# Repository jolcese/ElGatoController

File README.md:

# EL Gato Controller

  ## Description
  This is a standalone controller for the ElGato Lights. It's based on an ESP-WROOM-32 module but any ESP32 (or even ESP8266) should work with minimal changes.

  <figure><figcaption>Controller with Display and 3D Printed Case</figcaption></figure>
  <br>
  <br>
  <figure><figcaption>Schematic for the module, USB-UART controller and buttons</figcaption></figure>
  <br>
  <figure><figcaption>Display has been added after designing the PCB so no header/connector</figcaption></figure>
  <br>

  ## Table of Contents
  * [ToDo](#todo)
  * [Installation](#installation)
  * [Usage](#usage)
  * [License](#license)
  * [Contributing](#contributing)
  * [Tests](#tests)
  * [Questions](#questions)

  ## ToDo
  
  - NTP
  - Dynamic lights config/ Web Server
  - Shortcut reboot
  - Brightness
  - Faster REST
  - FIx BAR size
  - ~Wifi Portal~
  - ~OLED Status~
  ## Installation
  Some of the tools used to build this project
  - [Plaftormio](https://platformio.org/)
  - [Kicad](https://www.kicad.org/)
  ## Usage
  Currently, the IPs for both lights are hardcoded. Until I made that discoverable thru Bonjour, numbers of lights and IPs will need to be manually mofified.
  
    main.cpp
    
    const String sLight1 = "192.168.30.137";
    const String sLight2 = "192.168.30.161";

  ## License
  This project is license under MIT

  ## Contributing
  Nothing

  ## Tests
  no tests

  ## Questions
  If you have any questions about this projects, please contact me directly at jolcese@gmail.com. You can view more of my projects at https://github.com/jolcese.

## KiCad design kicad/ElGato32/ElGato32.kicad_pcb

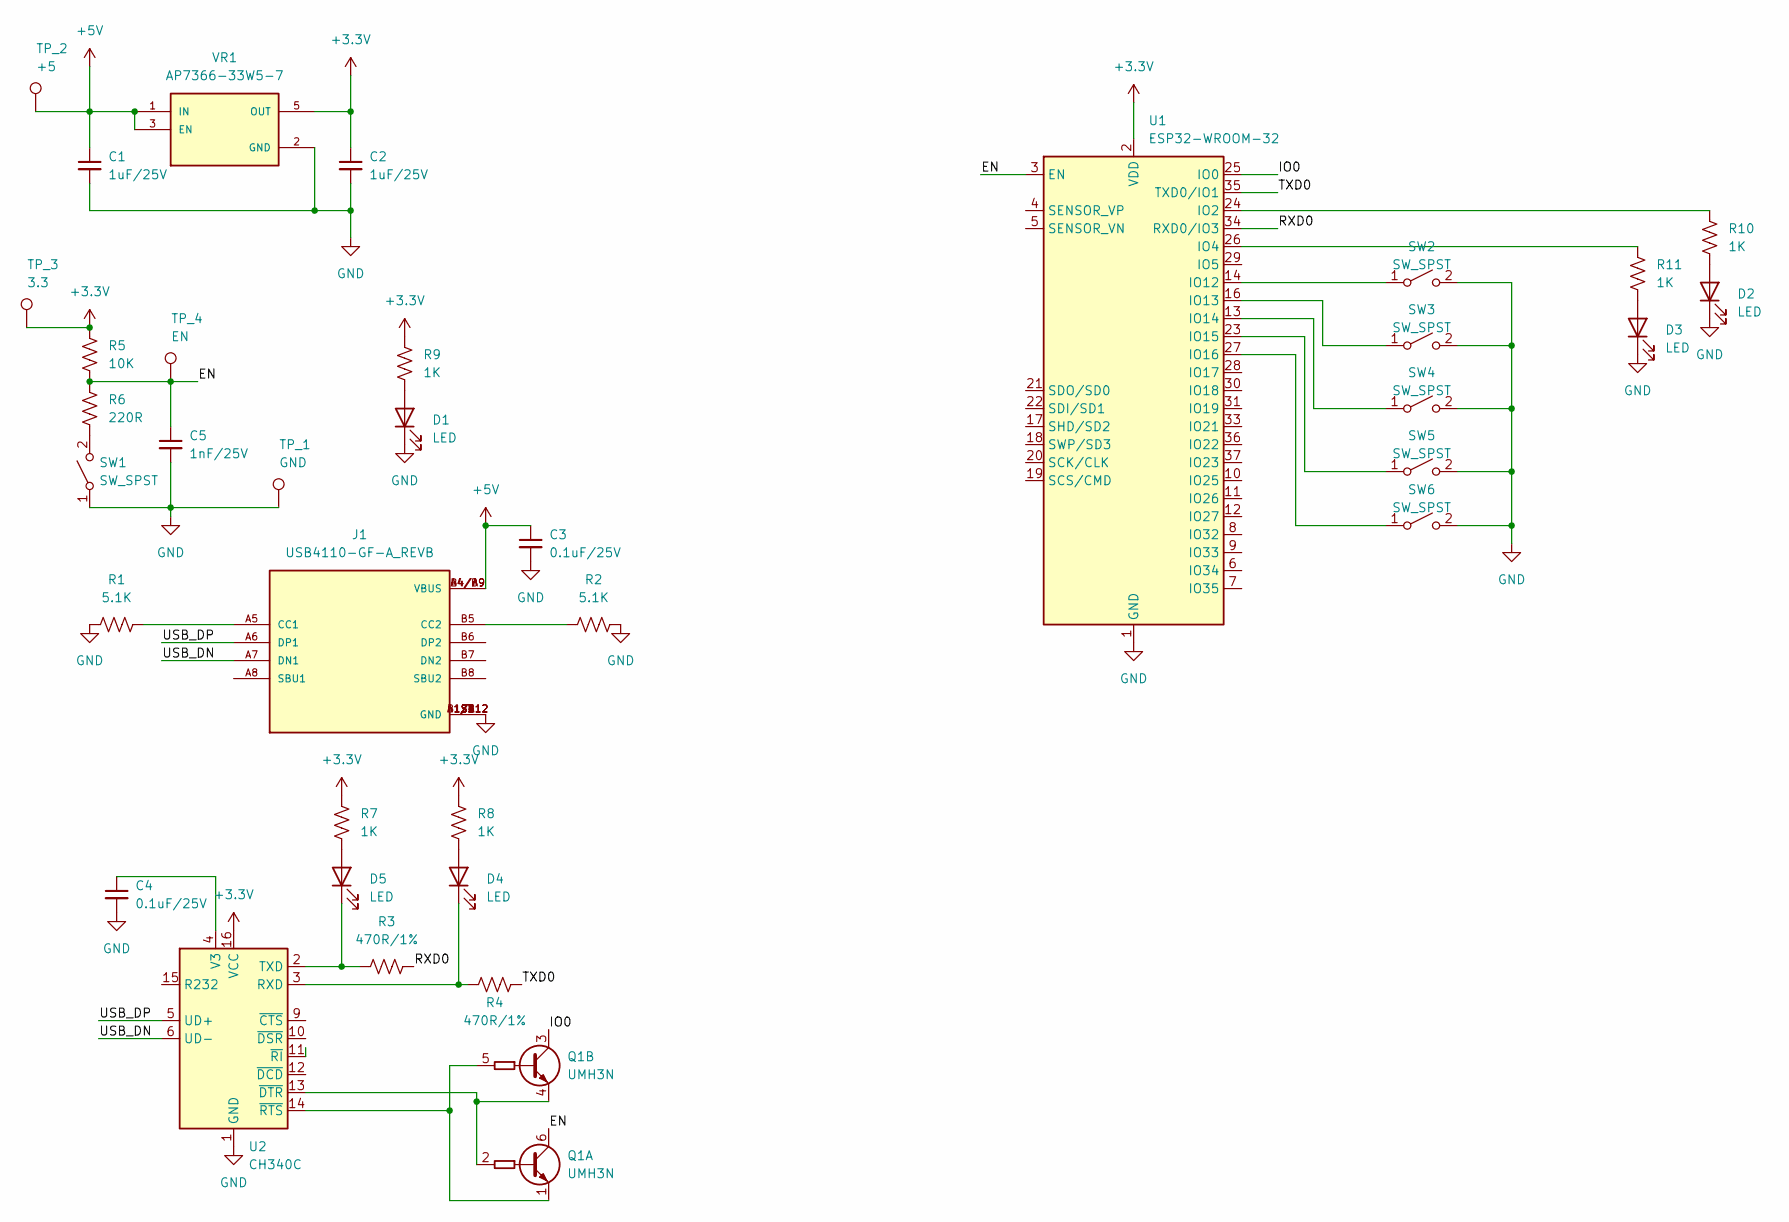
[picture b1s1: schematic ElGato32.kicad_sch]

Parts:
C1, C2: 1uF/25V; C_1206_3216Metric
C3, C4: 0.1uF/25V; C_1206_3216Metric
C5: 1nF/25V; C_1206_3216Metric
D1, D2, D3, D4, D5: LED; LED_1206_3216Metric_Pad1.42x1.75mm_HandSolder
J1: USB4110-GF-A_REVB; GCT_USB4110-GF-A_REVB; PARTREV B
Q1: UMH3N; SOT-363_SC-70-6
R1, R2: 5.1K; R_1206_3216Metric
R3, R4: 470R/1%; R_1206_3216Metric
R5: 10K; R_1206_3216Metric
R6: 220R; R_1206_3216Metric
R7, R8, R9, R10, R11: 1K; R_1206_3216Metric
SW1: SW_SPST; SW_B3U-3000P
SW2, SW3, SW4, SW5, SW6: SW_SPST; SW_PUSH-12mm
TP_1: GND; TestPoint_THTPad_1.5x1.5mm_Drill0.7mm
TP_2: +5; TestPoint_THTPad_1.5x1.5mm_Drill0.7mm
TP_3: 3.3; TestPoint_THTPad_1.5x1.5mm_Drill0.7mm
TP_4: EN; TestPoint_THTPad_1.5x1.5mm_Drill0.7mm
U1: ESP32-WROOM-32
U2: CH340C; SOIC-16_3.9x9.9mm_P1.27mm
VR1: AP7366-33W5-7; SOT95P285X140-5N; PARTREV 1-2

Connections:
+3.3V: C2.1, R5.2, R7.2, R8.2, R9.2, TP_3.1, U1.2 (VDD), U2.16 (VCC), VR1.5 (OUT)
+5V: C1.1, C3.1, J1.A4/B9 (VBUS), J1.B4/A9 (VBUS), TP_2.1, VR1.1 (IN), VR1.3 (EN)
/EN: C5.1, Q1.6 (C1), R5.1, R6.2, TP_4.1, U1.3 (EN)
/IO0: Q1.3 (C2), U1.25 (IO0)
/RXD0: R3.2, U1.34 (RXD0/IO3)
/TXD0: R4.2, U1.35 (TXD0/IO1)
/USB_DN: J1.A7 (DN1), U2.6 (UD-)
/USB_DP: J1.A6 (DP1), U2.5 (UD+)
GND: C1.2, C2.2, C3.2, C4.2, C5.2, D1.1 (K), D2.1 (K), D3.1 (K), J1.A1/B12 (GND), J1.B1/A12 (GND), J1.S1 (GND), J1.S2 (GND), J1.S3 (GND), J1.S4 (GND), R1.1, R2.2, SW1.1 (A), SW2.2 (B), SW3.2 (B), SW4.2 (B), SW5.2 (B), SW6.2 (B), TP_1.1, U1.1 (GND), U1.15 (GND), U1.38 (GND), U1.39 (GND), U2.1 (GND), VR1.2 (GND)
unnamed: D1.2 (A), R9.1
unnamed: D2.2 (A), R10.1
unnamed: D3.2 (A), R11.1
unnamed: D4.2 (A), R8.1
unnamed: D5.2 (A), R7.1
unnamed: Q1.1 (E1), Q1.5 (B2), U2.14 (~RTS)
unnamed: Q1.2 (B1), Q1.4 (E2), U2.13 (~DTR)
unnamed: J1.A5 (CC1), R1.2
unnamed: J1.B5 (CC2), R2.1
unnamed: D4.1 (K), R4.1, U2.3 (RXD)
unnamed: R6.1, SW1.2 (B)
unnamed: SW4.1 (A), U1.13 (IO14)
unnamed: SW2.1 (A), U1.14 (IO12)
unnamed: SW3.1 (A), U1.16 (IO13)
unnamed: SW5.1 (A), U1.23 (IO15)
unnamed: R10.2, U1.24 (IO2)
unnamed: R11.2, U1.26 (IO4)
unnamed: SW6.1 (A), U1.27 (IO16)
unnamed: D5.1 (K), R3.1, U2.2 (TXD)
unnamed: C4.1, U2.4 (V3)

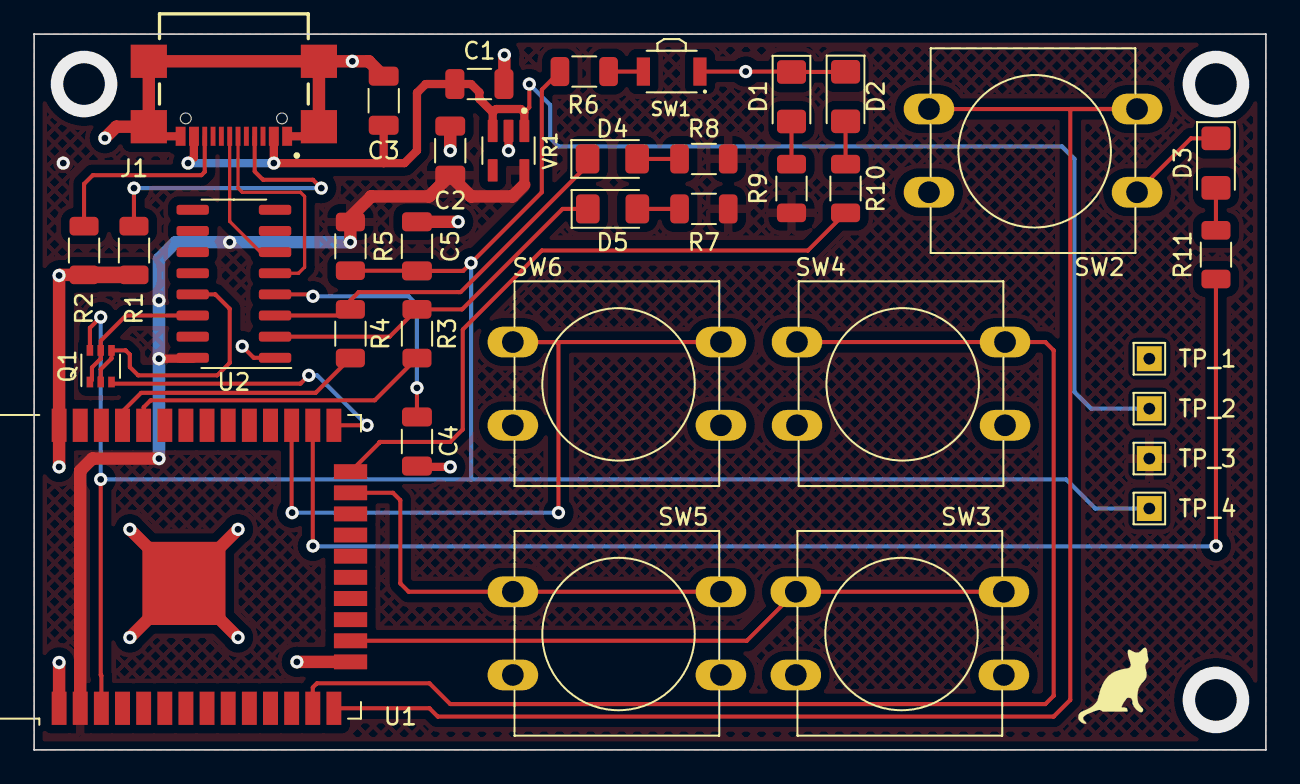
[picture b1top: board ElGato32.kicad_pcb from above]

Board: 2 copper layers, 74.0 x 43.0 mm, 36 parts (0 on the bottom side), 29 nets.

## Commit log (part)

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2022-09-28 Adding PlatformIO Code
2022-09-29 Use WifiManager lib directly from Github
2022-10-03 Adding datasheets
2022-10-03 Add README
2022-10-03 Add schematic
2022-10-03 Fixed readme
2022-11-11 Add retries

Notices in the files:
README.md:
License: MIT
